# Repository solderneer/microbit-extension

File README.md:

# microbit-extension
A microbit extension board to make it easier for kids to learn and use electronics

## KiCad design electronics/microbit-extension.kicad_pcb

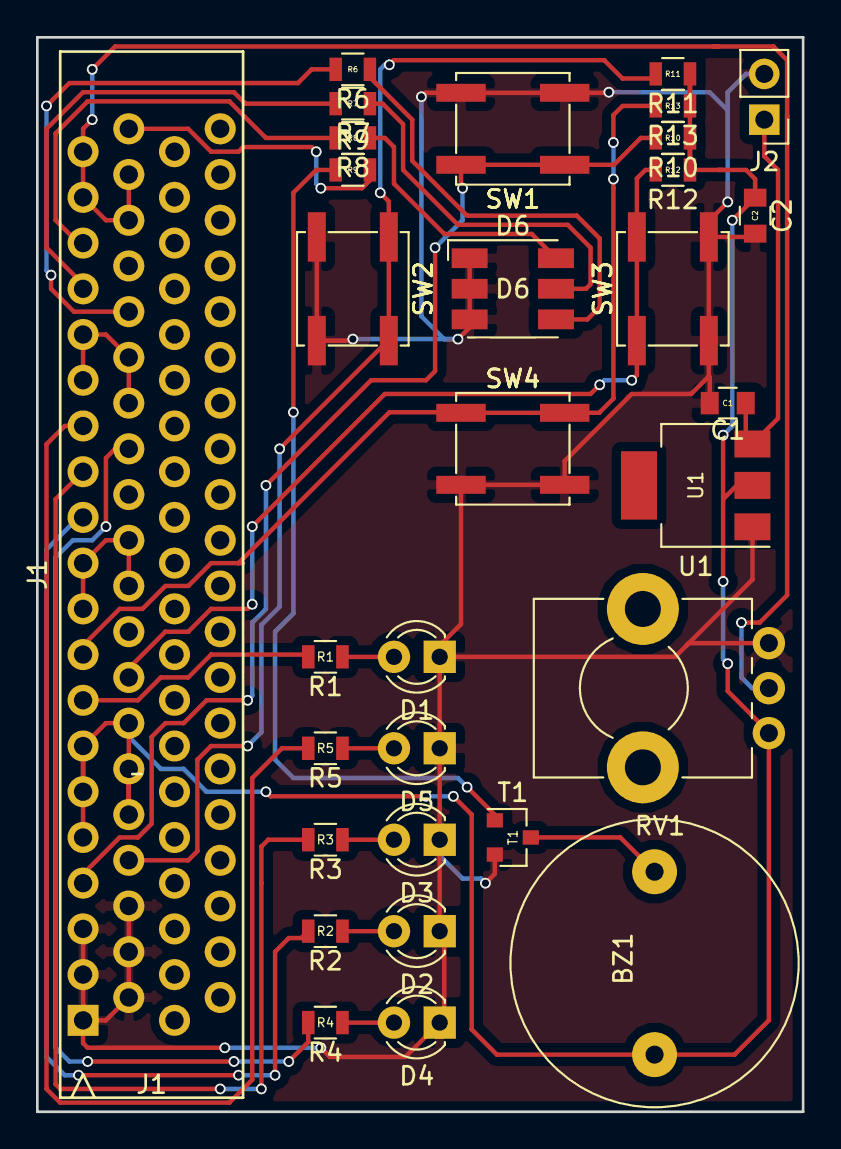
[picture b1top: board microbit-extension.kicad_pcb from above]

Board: 2 copper layers, 42.5 x 59.7 mm, 31 parts (0 on the bottom side), 29 nets.

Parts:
BZ1: Buzzer; BUZZER
C1: 100nF; C_0805
C2: 10uF; C_0805
D1, D2, D3, D4, D5: LED; LED_D3.0mm
D6: LED_RGB; LED_RGB_5050-6
J1: microbit_edge_connector; 4UCON_17909_02x401.27mm_Vertical
J2: 9V conn; Pin_Header_Straight_1x02_Pitch2.54mm
R1, R2, R3, R4, R5, R6, R7, R8, R10, R11, R12, R13: R; R_0805
R9: 1K; R_0805
RV1: POT; Potentiometer_Alps_RK09K_Horizontal
SW1, SW2, SW3, SW4: SW_DIP_x01; SW_SPST_EVPBF
T1: 2N4401; SOT-23
U1: LD1117S33CTR; SOT-223

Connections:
+3V3: BZ1.1, C2.1, J1.17, J1.19, J1.21, J1.23, J1.25, J1.27, R10.1, R11.1, R12.1, R13.1, RV1.3, U1.2
+9V: C1.1, J2.1, U1.3
/AI0: J1.71, J1.73, J1.75, J1.77, RV1.2
/AI1: J1.55, J1.57, J1.59, J1.61
/AI2: J1.37, J1.39, J1.41, J1.43
/BUZZER_PIN: J1.79, R9.2
/LED0: J1.29, R1.2
/LED1: J1.45, R2.2
/LED2: J1.49, R3.2
/LED3: J1.51, R4.2
/LED4: J1.53, R5.2
/RGBB: J1.63, R6.2
/RGBG: J1.65, R7.2
/RGBR: J1.69, R8.2
/SW1: J1.13, R10.2, SW1.1
/SW2: J1.15, R11.2, SW2.1
/SW3: J1.31, R12.2, SW3.1
/SW4: J1.33, R13.2, SW4.1
GND: C1.2, C2.2, D1.1, D2.1, D3.1, D4.1, D5.1, D6.1, D6.2, D6.3, J1.1, J1.3, J1.5, J1.7, J1.9, J1.11, J2.2, RV1.1, SW1.2, SW2.2, SW3.2, SW4.2, T1.2, U1.1
unnamed: BZ1.2, T1.3
unnamed: D1.2, R1.1
unnamed: D2.2, R2.1
unnamed: D3.2, R3.1
unnamed: D4.2, R4.1
unnamed: D5.2, R5.1
unnamed: D6.4, R6.1
unnamed: D6.5, R7.1
unnamed: D6.6, R8.1
unnamed: R9.1, T1.1

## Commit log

2017-08-05 added basic template
2017-08-05 added microbit libraries and started schematic
2017-08-05 schematics for buttons, LEDs and pot
2017-08-05 some notes on power consumption
2017-08-05 added LED buffers
2017-08-06 added LED driver and RGB LED
2017-08-06 more updated to schematics
2017-08-06 added buzzer driver transistor
2017-08-06 exported pdf
2017-08-06 more updates to schematics
2017-08-06 moved footprints to separate folder
2017-08-06 relative paths added
2017-08-07 footprint assignment
2017-08-07 moved in microbit connector footprint
2017-08-07 finished footprints
2017-08-07 removed temp files
2017-08-10 more updates to schematic
2017-08-10 added final local connections, need to check through
2017-08-10 starting layout
2017-08-10 need to redo and check the footprint association
2017-08-10 more layouting
2017-08-10 more layout planning
2017-08-10 a bit more routing work
2017-08-10 routing is more complete
2017-08-10 update to schematics
2017-08-10 finishing up routing
2017-08-11 finished up routing
2017-08-11 added copperpours
2017-08-12 caching footprints
2017-08-12 fixed silkscreen
2017-08-12 fixed most things
2017-08-13 updated to schematics
2017-08-13 caching library files
2017-08-21 generated gerbers
2017-08-24 combined drill files, ready for production
